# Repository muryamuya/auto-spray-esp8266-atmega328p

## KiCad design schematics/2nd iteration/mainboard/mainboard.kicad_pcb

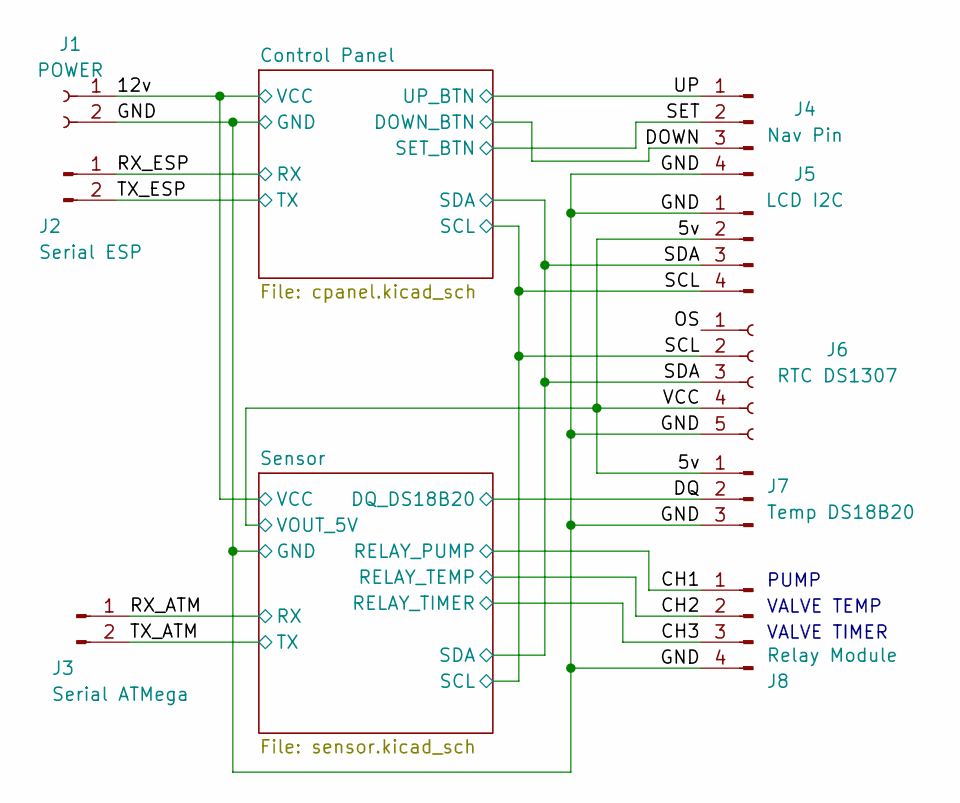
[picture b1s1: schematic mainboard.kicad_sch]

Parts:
J1: POWER; TerminalBlock_bornier-2_P5.08mm
J2: Serial ESP; PinHeader_1x02_P2.54mm_Vertical
J3: Serial ATMega; PinHeader_1x02_P2.54mm_Vertical
J4: Nav Pin; PinHeader_1x04_P2.54mm_Vertical
J5: LCD I2C; PinHeader_1x04_P2.54mm_Vertical
J6: RTC DS1307; PinSocket_1x05_P2.54mm_Vertical
J7: Temp DS18B20; PinHeader_1x03_P2.54mm_Vertical
J8: Relay Module; PinHeader_1x04_P2.54mm_Vertical

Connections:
/5v: J5.2, J6.4, J7.1; also elsewhere on the board
/12v: J1.1; also elsewhere on the board
/CH1: J8.1; also elsewhere on the board
/CH2: J8.2; also elsewhere on the board
/CH3: J8.3; also elsewhere on the board
/DOWN: J4.3; also elsewhere on the board
/DQ: J7.2; also elsewhere on the board
/GND: J1.2, J4.4, J5.1, J6.5, J7.3, J8.4; also elsewhere on the board
/OS: J6.1
/RX_ATM: J3.1; also elsewhere on the board
/RX_ESP: J2.1; also elsewhere on the board
/SCL: J5.4, J6.2; also elsewhere on the board
/SDA: J5.3, J6.3; also elsewhere on the board
/SET: J4.2; also elsewhere on the board
/TX_ATM: J3.2; also elsewhere on the board
/TX_ESP: J2.2; also elsewhere on the board
/UP: J4.1; also elsewhere on the board

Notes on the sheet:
VALVE TIMER
VALVE TEMP
PUMP

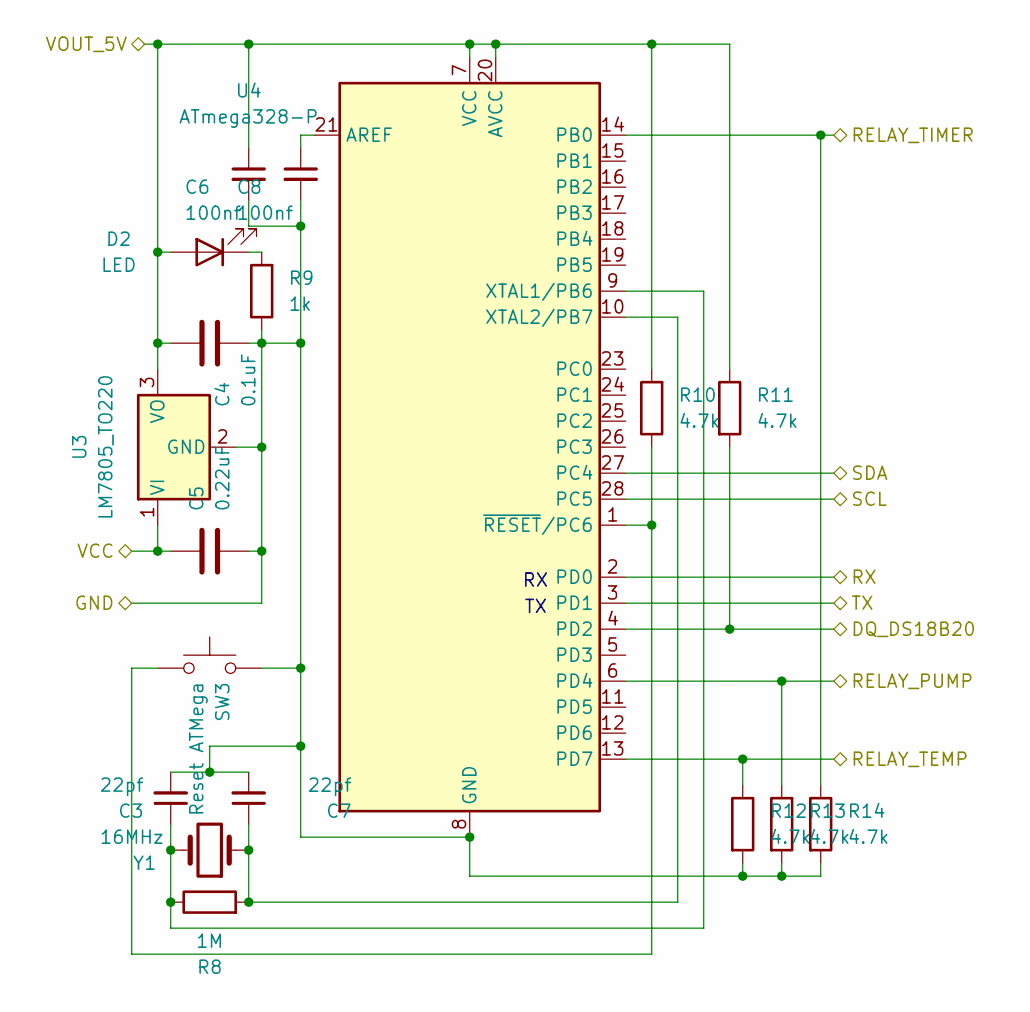
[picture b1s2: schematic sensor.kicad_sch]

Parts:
C3, C7: 22pf; C_Disc_D4.7mm_W2.5mm_P5.00mm
C4: 0.1uF; C_Disc_D4.7mm_W2.5mm_P5.00mm
C5: 0.22uF; C_Disc_D4.7mm_W2.5mm_P5.00mm
C6, C8: 100nf; C_Disc_D4.7mm_W2.5mm_P5.00mm
D2: LED; LED_D5.0mm
R8: 1M; R_Axial_DIN0207_L6.3mm_D2.5mm_P7.62mm_Horizontal
R9: 1k; R_Axial_DIN0207_L6.3mm_D2.5mm_P7.62mm_Horizontal
R10, R11, R12, R13, R14: 4.7k; R_Axial_DIN0207_L6.3mm_D2.5mm_P7.62mm_Horizontal
SW3: Reset ATMega; SW_PUSH_6mm
U3: LM7805_TO220; TO-220-3_Horizontal_TabDown
U4: ATmega328-P; DIP-28_W7.62mm
Y1: 16MHz; Crystal_HC49-U_Vertical

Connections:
/5v: C4.1, C6.1, D2.2 (A), R10.2, R11.1, U3.3 (VO), U4.7 (VCC), U4.20 (AVCC); also elsewhere on the board
/12v: C5.1, U3.1 (VI); also elsewhere on the board
/CH1: R13.1, U4.6 (PD4); also elsewhere on the board
/CH2: R12.1, U4.13 (PD7); also elsewhere on the board
/CH3: R14.1, U4.14 (PB0); also elsewhere on the board
/DQ: R11.2, U4.4 (PD2); also elsewhere on the board
/GND: C3.2, C4.2, C5.2, C6.2, C7.2, C8.2, R9.1, R12.2, R13.2, R14.2, SW3.1, U3.2 (GND), U4.8 (GND), U4.22 (GND); also elsewhere on the board
/RX_ATM: U4.2 (PD0); also elsewhere on the board
/SCL: U4.28 (PC5); also elsewhere on the board
/SDA: U4.27 (PC4); also elsewhere on the board
/TX_ATM: U4.3 (PD1); also elsewhere on the board
unnamed: C3.1, R8.1, U4.9 (XTAL1/PB6), Y1.2
unnamed: C7.1, R8.2, U4.10 (XTAL2/PB7), Y1.1
unnamed: C8.1, U4.21 (AREF)
unnamed: D2.1 (K), R9.2
unnamed: R10.1, SW3.2, U4.1 (~RESET/PC6)

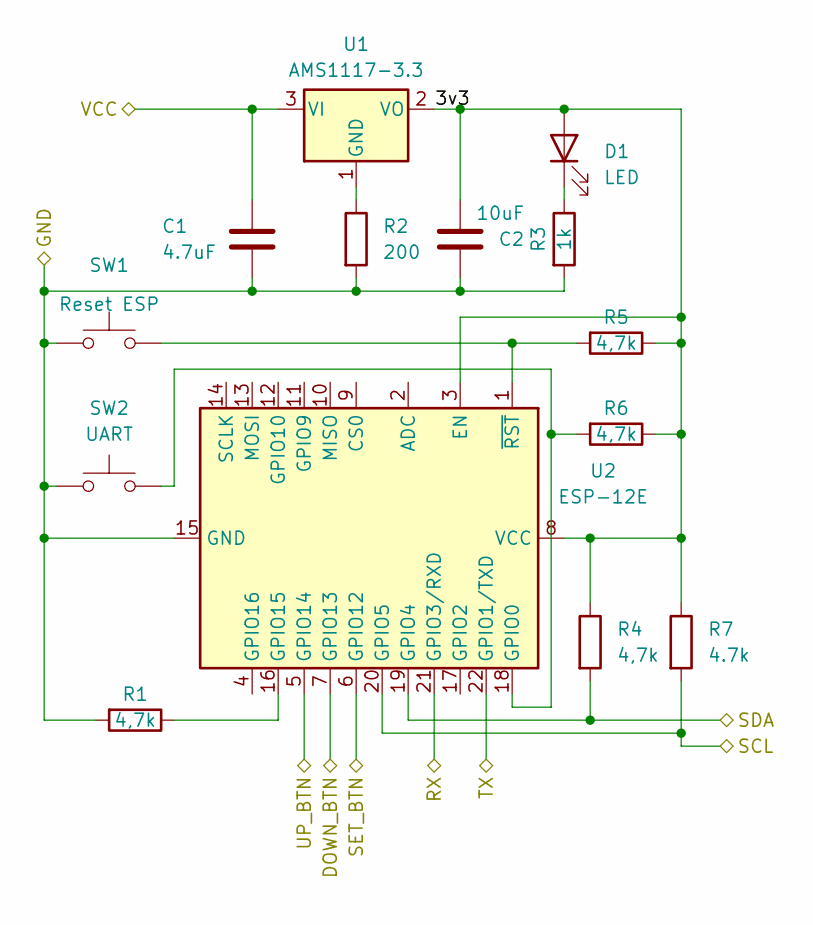
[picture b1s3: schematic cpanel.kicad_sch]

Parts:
C1: 4.7uF; C_Disc_D4.7mm_W2.5mm_P5.00mm
C2: 10uF; C_Disc_D4.7mm_W2.5mm_P5.00mm
D1: LED; LED_D5.0mm
R1, R4, R5, R6: 4,7k; R_Axial_DIN0207_L6.3mm_D2.5mm_P7.62mm_Horizontal
R2: 200; R_Axial_DIN0207_L6.3mm_D2.5mm_P7.62mm_Horizontal
R3: 1k; R_Axial_DIN0207_L6.3mm_D2.5mm_P7.62mm_Horizontal
R7: 4.7k; R_Axial_DIN0207_L6.3mm_D2.5mm_P7.62mm_Horizontal
SW1: Reset ESP; SW_PUSH_6mm
SW2: UART; SW_PUSH_6mm
U1: AMS1117-3.3; SOT-223-3_TabPin2
U2: ESP-12E

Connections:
/12v: C1.2, U1.3 (VI); also elsewhere on the board
/Control Panel/3v3: C2.2, D1.2 (A), R4.1, R5.1, R6.1, R7.1, U1.2 (VO), U2.3 (EN), U2.8 (VCC)
/DOWN: U2.7 (GPIO13); also elsewhere on the board
/GND: C1.1, C2.1, R1.2, R2.2, R3.2, SW1.1, SW2.1, U2.15 (GND); also elsewhere on the board
/RX_ESP: U2.21 (GPIO3/RXD); also elsewhere on the board
/SCL: R7.2, U2.20 (GPIO5); also elsewhere on the board
/SDA: R4.2, U2.19 (GPIO4); also elsewhere on the board
/SET: U2.6 (GPIO12); also elsewhere on the board
/TX_ESP: U2.22 (GPIO1/TXD); also elsewhere on the board
/UP: U2.5 (GPIO14); also elsewhere on the board
unnamed: D1.1 (K), R3.1
unnamed: R1.1, U2.16 (GPIO15)
unnamed: R2.1, U1.1 (GND)
unnamed: R5.2, SW1.2, U2.1 (~RST)
unnamed: R6.2, SW2.2, U2.18 (GPIO0)

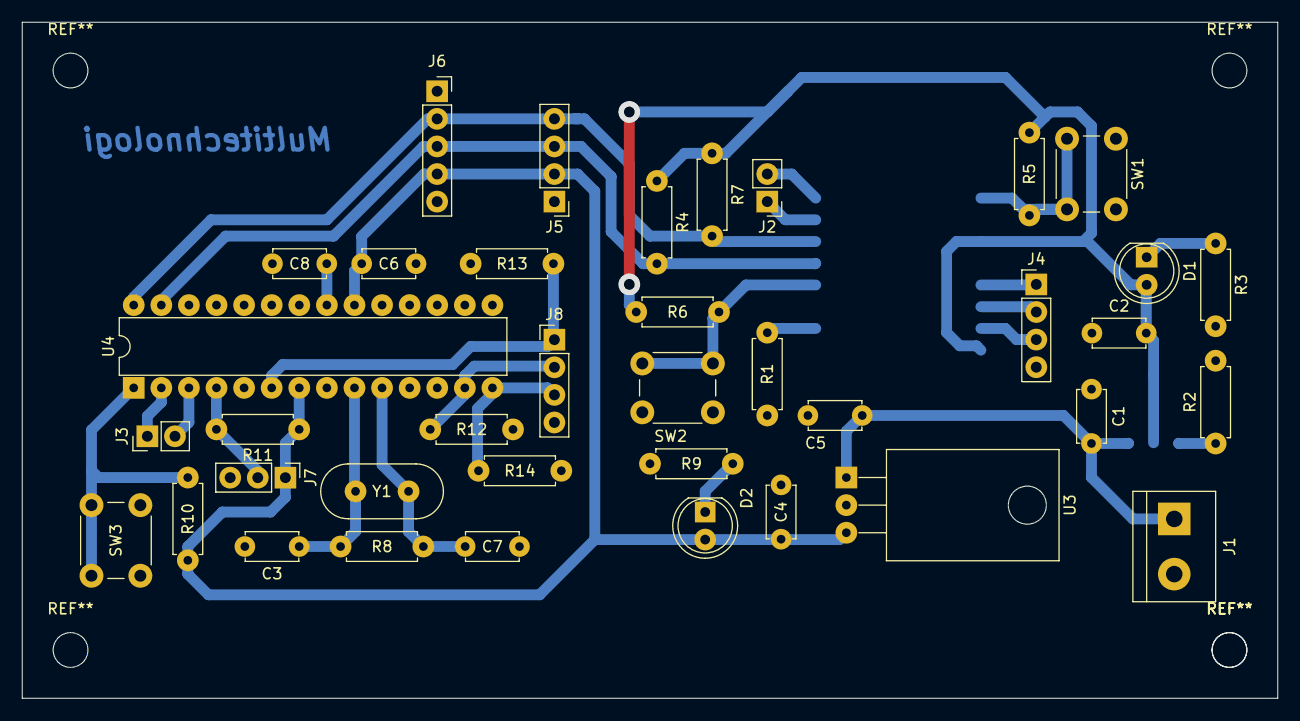
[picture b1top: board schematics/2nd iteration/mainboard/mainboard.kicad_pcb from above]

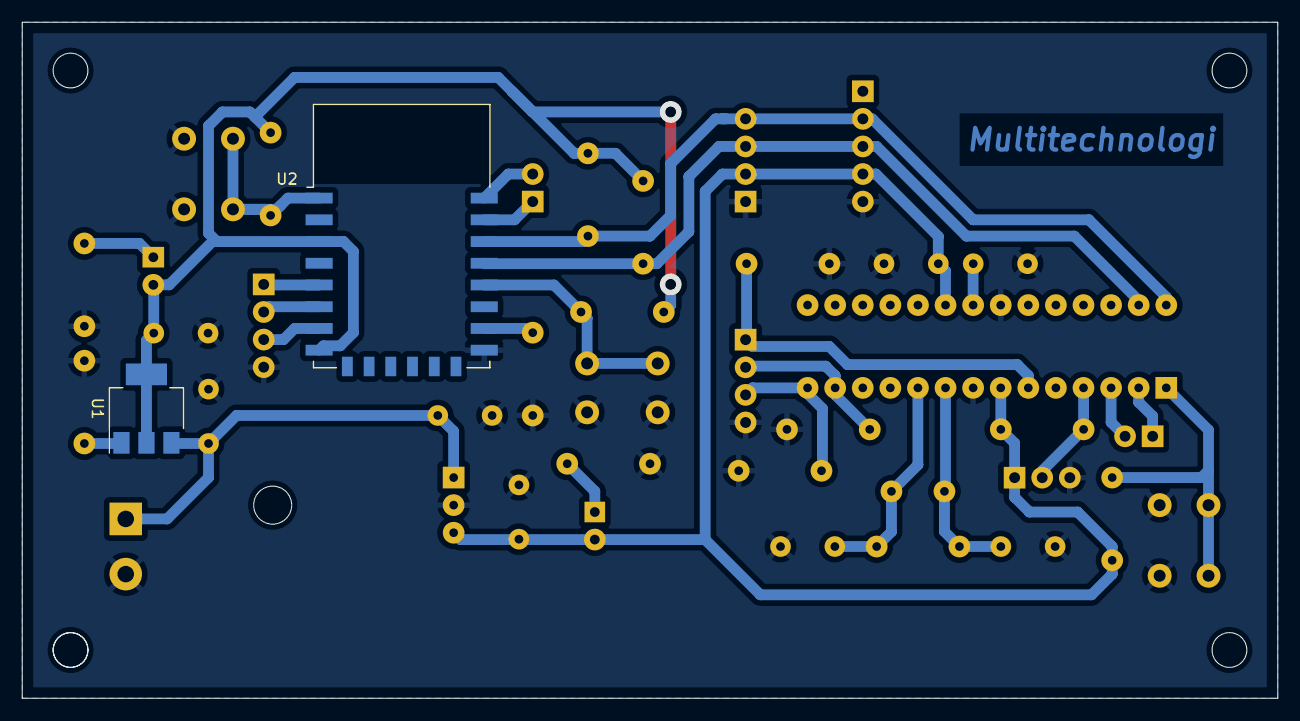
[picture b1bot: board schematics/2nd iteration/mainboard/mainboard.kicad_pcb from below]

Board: 2 copper layers, 115.6 x 62.2 mm, 40 parts (2 on the bottom side), 27 nets.

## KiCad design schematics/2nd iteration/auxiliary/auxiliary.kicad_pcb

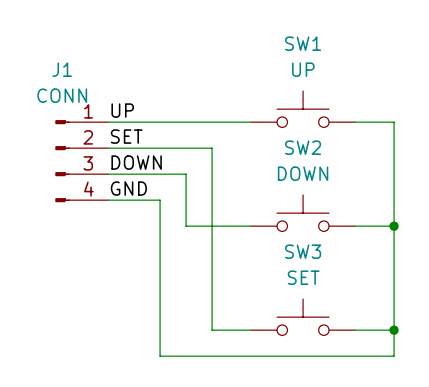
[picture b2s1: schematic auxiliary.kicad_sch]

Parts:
J1: CONN; PinHeader_1x04_P2.54mm_Horizontal
SW1: UP; SW_PUSH_6mm
SW2: DOWN; SW_PUSH_6mm
SW3: SET; SW_PUSH_6mm

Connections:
/DOWN: J1.3, SW2.1
/GND: J1.4, SW1.2, SW2.2, SW3.2
/SET: J1.2, SW3.1
/UP: J1.1, SW1.1

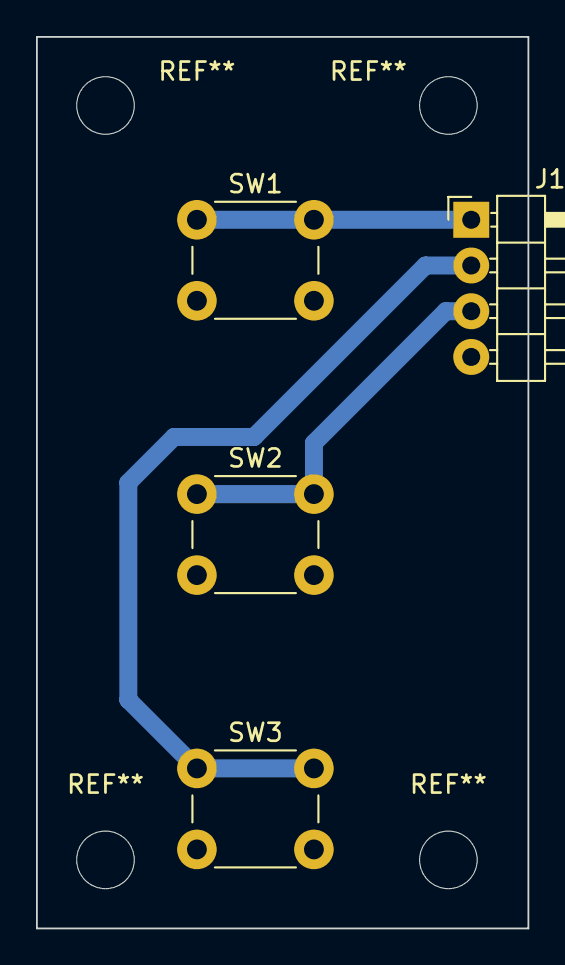
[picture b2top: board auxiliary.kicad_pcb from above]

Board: 2 copper layers, 27.3 x 49.5 mm, 4 parts (0 on the bottom side), 4 nets.

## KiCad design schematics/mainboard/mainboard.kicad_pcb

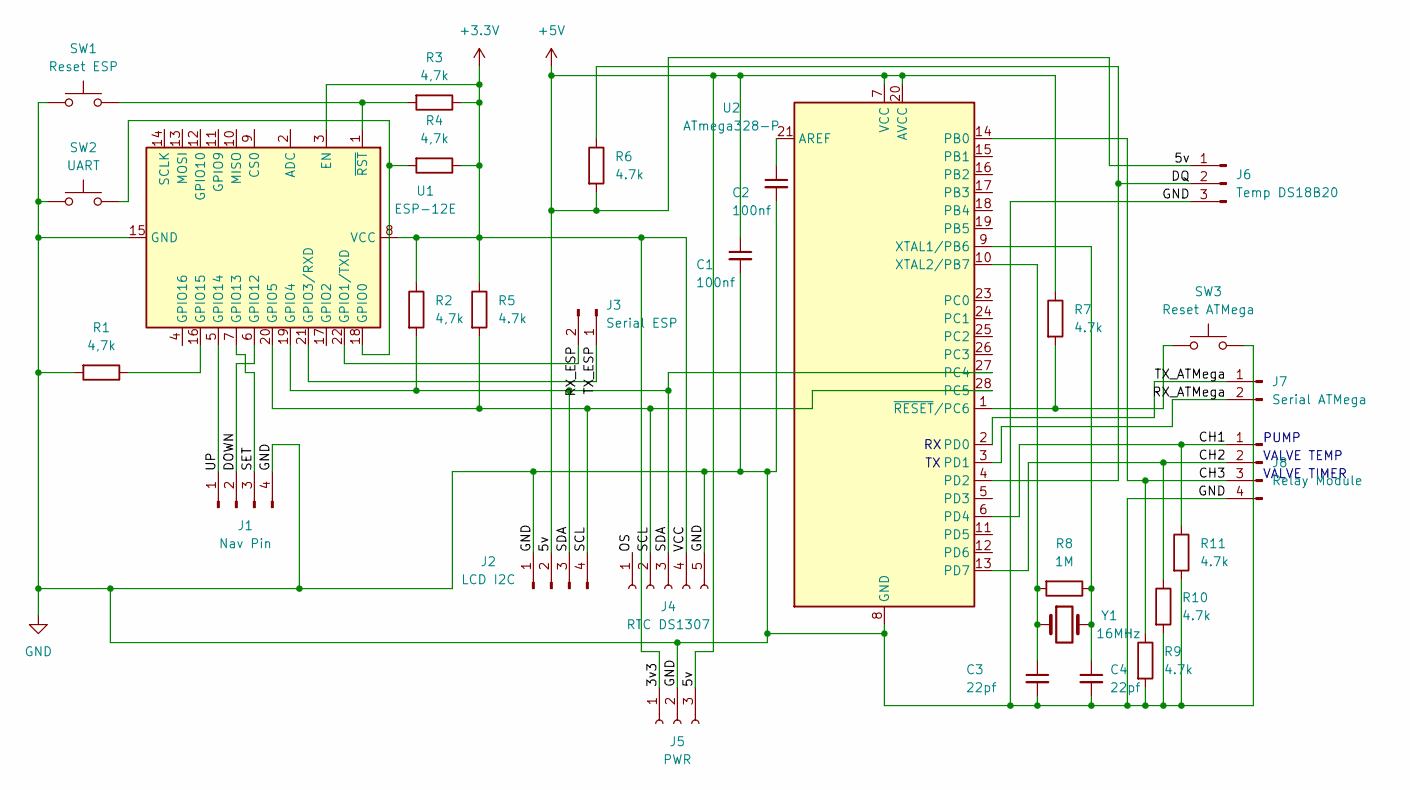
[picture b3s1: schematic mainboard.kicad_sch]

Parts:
C1, C2: 100nf; C_Disc_D4.7mm_W2.5mm_P5.00mm
C3, C4: 22pf; C_Disc_D4.7mm_W2.5mm_P5.00mm
J1: Nav Pin; PinHeader_1x04_P2.54mm_Vertical
J2: LCD I2C; PinHeader_1x04_P2.54mm_Vertical
J3: Serial ESP; PinHeader_1x02_P2.54mm_Vertical
J4: RTC DS1307; PinSocket_1x05_P2.54mm_Vertical
J5: PWR; TerminalBlock_bornier-3_P5.08mm
J6: Temp DS18B20; PinHeader_1x03_P2.54mm_Vertical
J7: Serial ATMega; PinHeader_1x02_P2.54mm_Vertical
J8: Relay Module; PinHeader_1x04_P2.54mm_Vertical
R1, R2, R3, R4: 4,7k; R_Axial_DIN0207_L6.3mm_D2.5mm_P7.62mm_Horizontal
R5, R6, R7, R9, R10, R11: 4.7k; R_Axial_DIN0207_L6.3mm_D2.5mm_P7.62mm_Horizontal
R8: 1M; R_Axial_DIN0207_L6.3mm_D2.5mm_P7.62mm_Horizontal
SW1: Reset ESP; SW_PUSH_6mm
SW2: UART; SW_PUSH_6mm
SW3: Reset ATMega; SW_PUSH_6mm
U1: ESP-12E
U2: ATmega328-P; DIP-28_W7.62mm
Y1: 16MHz; Crystal_HC49-U_Vertical

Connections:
+3.3V: J4.4, J5.1, R2.1, R3.1, R4.1, R5.1, U1.3 (EN), U1.8 (VCC)
+5V: C1.1, J2.2, J5.3, J6.1, R6.2, R7.1, U2.7 (VCC), U2.20 (AVCC)
/CH1: J8.1, R11.1, U2.6 (PD4)
/CH2: J8.2, R10.1, U2.13 (PD7)
/CH3: J8.3, R9.1, U2.14 (PB0)
/DOWN: J1.2, U1.6 (GPIO12)
/DQ: J6.2, R6.1, U2.4 (PD2)
/OS: J4.1
/RX_ATMega: J7.2, U2.3 (PD1)
/RX_ESP: J3.2, U1.22 (GPIO1/TXD)
/SCL: J2.4, J4.2, R5.2, U1.20 (GPIO5), U2.28 (PC5)
/SDA: J2.3, J4.3, R2.2, U1.19 (GPIO4), U2.27 (PC4)
/SET: J1.3, U1.7 (GPIO13)
/TX_ATMega: J7.1, U2.2 (PD0)
/TX_ESP: J3.1, U1.21 (GPIO3/RXD)
/UP: J1.1, U1.5 (GPIO14)
GND: C1.2, C2.2, C3.2, C4.2, J1.4, J2.1, J4.5, J5.2, J6.3, J8.4, R1.2, R9.2, R10.2, R11.2, SW1.1, SW2.1, SW3.1, U1.15 (GND), U2.8 (GND), U2.22 (GND)
unnamed: C2.1, U2.21 (AREF)
unnamed: C3.1, R8.2, U2.10 (XTAL2/PB7), Y1.1
unnamed: C4.1, R8.1, U2.9 (XTAL1/PB6), Y1.2
unnamed: R1.1, U1.16 (GPIO15)
unnamed: R3.2, SW1.2, U1.1 (~RST)
unnamed: R4.2, SW2.2, U1.18 (GPIO0)
unnamed: R7.2, SW3.2, U2.1 (~RESET/PC6)

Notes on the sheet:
VALVE TIMER
VALVE TEMP
PUMP

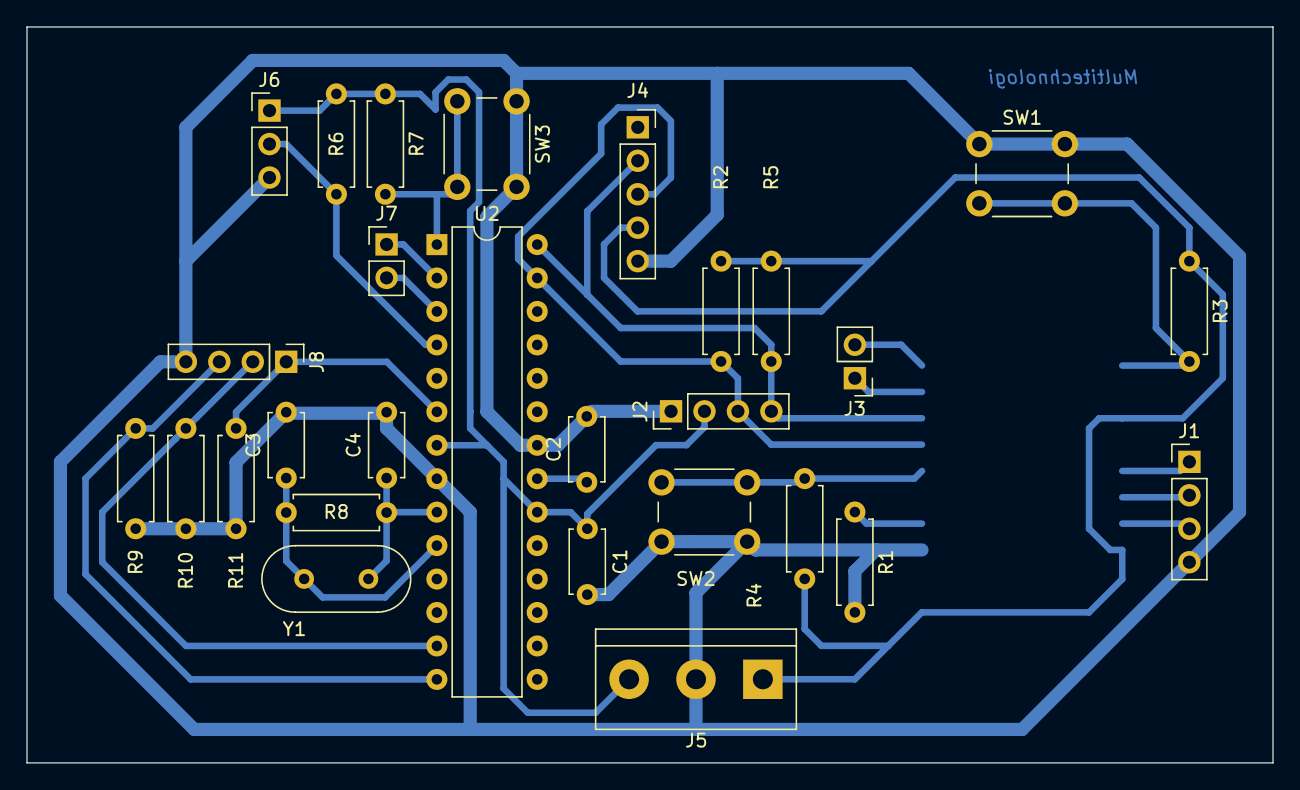
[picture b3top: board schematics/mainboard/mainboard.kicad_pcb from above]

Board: 2 copper layers, 94.6 x 55.9 mm, 29 parts (1 on the bottom side), 23 nets.

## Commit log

2022-10-18 Initial add
    Adding project files to repo
2022-10-19 tidying the code, add menu
2022-10-19 removed libraries and add vscode settings
2022-10-19 rework folder structure, need convert ino to cpp
2022-10-20 remove unused vscode settings
2022-10-20 converted ino to cpp and reworked lib
2022-10-20 finishing menu, work on backlight, menu functions
2022-10-21 backlight and sub reciever still bugged
2022-10-24 add debugging function
2022-10-24 fixed var overflow, backlight, rollover millis
2022-10-24 renamed repo
2022-10-26 renamed files
2022-11-02 added schematic, updated index.html and filesys
2022-11-02 renamed sub to aux, update logo alpha
2022-11-08 edited index.html, added html processor
2022-11-09 HTML update script, main update POST GET requests
2022-11-11 finishing the code, all functioning
2022-11-14 changed esp response from plain to html
2022-11-14 fix schematics, added button schematics
2022-11-18 added LICENSE
2022-11-18 minor edit
2022-11-18 cleanup, added net labels
2022-12-01 minor fix schematics
2023-01-04 added usbasp upload config
2023-01-12 added debugging uart and rework board
2023-02-01 main fixed debugging delay, aux add fault prevent
